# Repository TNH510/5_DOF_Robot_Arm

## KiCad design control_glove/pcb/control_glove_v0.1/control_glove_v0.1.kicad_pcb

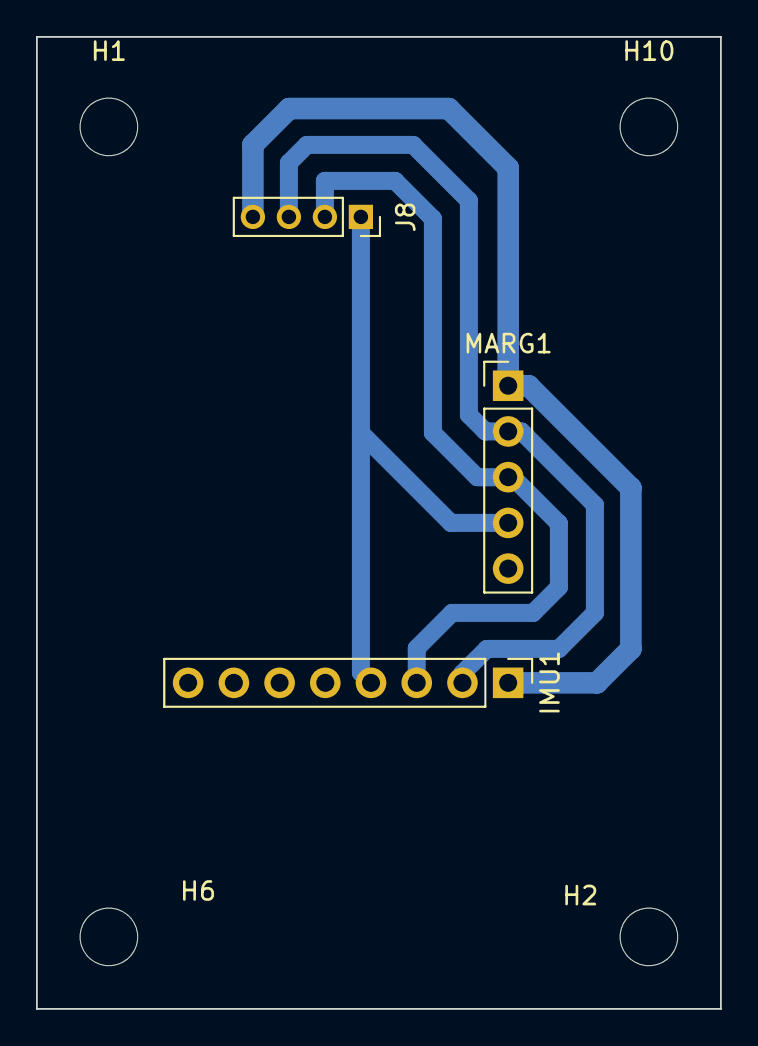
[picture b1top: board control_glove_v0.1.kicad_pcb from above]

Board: 2 copper layers, 38.0 x 54.0 mm, 7 parts (0 on the bottom side), 4 nets.

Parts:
H1, H2, H6, H10: MountingHole; MountingHole_3.2mm_M3
IMU1: GY-521; PinHeader_1x08_P2.54mm_Vertical
J8: Conn_01x04_Female; PinSocket_1x04_P2.00mm_Vertical
MARG1: HMC5883L; PinHeader_1x05_P2.54mm_Vertical

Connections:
unnamed: IMU1.1 (VCC), J8.4, MARG1.1 (VCC)
unnamed: IMU1.2 (GND), J8.3, MARG1.2 (GND)
unnamed: IMU1.3 (SCL), J8.2, MARG1.3 (SCL)
unnamed: IMU1.4 (SDA), J8.1, MARG1.4 (SDA)

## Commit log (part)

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2024-03-16 update: Design angle control schematic
2024-03-16 update: Angle follow set point success
2024-03-16 update: Add SFC program 6
2024-03-16 update: Test image processing on Matlab
2024-03-16 update: Add adapt 5 axis
2024-03-16 update: Control robot using apdative control through uart
2024-03-16 update: Test z_pos control adapt success
2024-03-17 update: Apply madgwickAHRS for IMU and MARG success
2024-03-17 update: finish detect edge image
2024-03-17 update: Optimize uart receive
2024-03-17 update: Optimize code for GUI
2024-03-17 update: Remove start frame
2024-03-23 update: Meeting 23/03
2024-03-23 update: Components list and caculate prices
2024-03-23 update: Complete schematic design
2024-03-23 fix: Merge conflict
2024-03-24 update: Test marg sensor calib
2024-03-24 Update: Done detect egde by canny method
2024-03-24 Update: change name function
2024-03-29 update: Calib IMU success
2024-03-30 update: Add QMC5883L datasheet
2024-03-30 update: Add QMC5883L sensor files
2024-03-30 update: Get MARG data success
2024-03-31 update: Read ADC very success
2024-03-31 update: setting.json
2024-03-31 Delete
2024-04-03 update: Change clock from 64 Mhz to 80 Mhz
2024-04-05 Update: complete Hough Transform
2024-04-05 update: Test quaternion
2024-04-06 update: Success caculate forward kinematic for glove
2024-04-06 Update: Success drawing edges
2024-04-06 update: Success caculate and display x, y, z pos from glove (need improve)
2024-04-07 update: Add MPU9250 files to reference
2024-04-07 update: Delete uneccessary files
2024-04-07 update: add comment code
2024-04-07 update: Complete list and connect all components
2024-04-07 update: Pins for PCB
2024-04-12 update: PCB setup and arange component positions
2024-04-13 update: Complete merging image processing
2024-04-14 update: Complete fix pcb
2024-04-15 update: Excel file
2024-04-15 refactor: Clean all
2024-04-18 update: Success calib for shoulder IMU
2024-04-18 update: Success calib for shoulder MARG
2024-04-18 update: Add low pass filter average for RV1
2024-04-18 fix: Wireless UART module do not respone
    Set Pin need to HIGH
2024-04-18 update: Add Wireless UART module note
2024-04-19 update: Success encrypt and decrypt data between device and MATLAB
2024-04-19 update: Test with python
2024-04-19 update: Complete test kinematic with shoulder and elbow
2024-04-20 update: Control glove space (not correct l1, l2)
2024-04-20 update: Test robot pos convert
2024-04-21 update: Add invert kinematic function
2024-04-21 update: Complete basic glove hardware v0.1 (need fixed size)
2024-05-02 ADD: file Testing Otsu's Method
2024-05-04 update: Update position and show on robot in GUI
2024-05-04 update: Optimize data transmission speed for UART
2024-05-04 Update: Apply Otsu method success.
2024-05-05 update: Vo pin
2024-05-05 update: Modify the limitation for angle of robot
2024-05-05 fix: Limitation for Z axis
2024-05-05 update: Try to use glove to control real Robot
2024-05-05 update: Test control robot over glove successfully
2024-05-05 Update: Success Auto Thresholding
2024-05-05 update: Create function for MoveL
2024-05-07 update: clear Hough Threshold.text
2024-05-07 Update: Copy file WindowApp to Image_processing
2024-05-07 update: Create trajectory for real Robot control
2024-05-07 fix: Change the TCP/IP port
2024-05-09 Update: convert from winform app to console app
2024-05-10 update: Design the transmission system at the wrist join
2024-05-10 update: Add basic content to control glove documents
2024-05-11 update: Create function to write angle data to plc
2024-05-11 update: Finish creating function to move 3 points for robot
2024-05-11 update: Add function in timer in order to test
2024-05-11 fix: Delete 1 line due to duplication
2024-05-11 update: Add glove_v0.1_part_1
2024-05-12 update: Change plc program
2024-05-12 update: Add 2 gear for control glove
2024-05-15 update: Add hole for imu module wires
2024-05-17 update: Change pcb size to 38 x 100
2024-05-18 update: Complete connect thanh_cang_tay and thanh_khuy_tay
2024-05-18 update: nothing
2024-05-18 update: Upload which need to be done for protect capstone project
2024-05-19 update: Add autocad file for mica cutting
2024-05-19 update: Connect all component completely
2024-05-19 update: Delete over defined error
2024-05-23 Update:Display the corner on Image
2024-05-24 update: Prepare files for mica cutting and 3d printing
2024-05-24 Update: complete calculate Mid Point object and angle object
2024-05-25 update: Finish testing move mutliple points with MoveJ
2024-05-25 update: Add element to control theta 5
2024-05-25 update: Re-cut mica
2024-05-26 update: Create robot_data for trajectory planning
2024-05-26 update: Transfer program from winform to console
2024-05-26 update: Export Japcobian Plus result
2024-05-26 update: Create function to move every 10 points
2024-05-31 update: Add SW1 and SW2 success
2024-05-31 update: Change UART module settings to reduce power consumption and I2C issues cause by lack of power
2024-06-01 update: Create workitem to do
2024-06-01 Update: Detect shape
2024-06-01 Nothing
2024-06-01 update: I'm try my best to filter noise in image, ye?
2024-06-02 fix: UART position data always zero
2024-06-02 update: Add crc-8-atm
2024-06-06 update: Bills for all
2024-06-06 update: Optimize uart module send 19 bytes at one time and use 210 ms
2024-06-07 update: Complete update nap pin
2024-06-07 update: Export .stl files
2024-06-07 update: Add 2D drawing for thanh cang tay, thanh khuyy tay and thanh noi
2024-06-08 update: Create python file to show raw data on graph
2024-06-08 update: Demonstrate the method of linear regression and circular regression
2024-06-09 docs: Update to design control robot arm algorithm
2024-06-09 update: Add K7 program to control velocity
2024-06-09 update: Add K7 program to control velocity Add adaptive velocity control
2024-06-09 update: Check jacobi
2024-06-09 update: Create function to using adaptive control with controlling velocity
2024-06-09 update: Test receive UART success
2024-06-09 update: Rename robot tool gui folder
2024-06-10 update: Fix conflict for gui c#
2024-06-10 update: Test linear regression function sucessfully
2024-06-10 fix: UART break when move control glove
2024-06-11 update: Add function to save polynomial_regression.csv
2024-06-14 update: Add custom gear 6 mm
2024-06-14 update: Add bearing 6 mm
2024-06-15 update: Save velocity and position to .csv file success
2024-06-15 update: omega 1, omega 2, omega look like stable
2024-06-15 update: Discovery new feature -- TabControl
2024-06-15 update: Create polynomial regression completely
2024-06-16 update: Create the final ver for image processing
2024-06-16 update: Enable velocity control
2024-06-16 fix: Velocity do not transmit to plc
2024-06-16 update: Not send stream command when hold left button
2024-06-16 update: Enable write to csv
2024-06-16 update: Reset raw data for test.csv
2024-06-16 update: Add hieu_packet to test uart
2024-06-17 update: Optimize GUI
2024-06-17 update: polynomial_regression on matlab
2024-06-17 update: test polyomial regression on matlab
2024-06-17 update: Test UART failed, need to optimize C#
2024-06-17 fix: UART error fixed
2024-06-17 update: Optimize low vel control
2024-06-18 docs: Add 6mm bearing datasheet
2024-06-19 update: Done the polynomial regression
2024-06-19 update: Complete basic concept design of v0.3
2024-06-19 update: Still facing polynomial regression algorthim
2024-06-20 update: Add red and green button
2024-06-20 update: detect point in hough matrix
2024-06-21 update: Optimize min angle to 60 degrees
2024-06-21 update: Fix all bug
2024-06-21 update: Clean code
2024-06-21 update: Add driver to control LED
2024-06-22 update: Test change system mode success
2024-06-22 update: Test send encode data success
2024-06-22 fix: Bug in low pass filter
2024-06-22 update: Add STL for 2 part of control glove
2024-06-22 update: Create low pass filter for stable the input data
2024-06-22 update: Success import glove.stl to view
2024-06-22 update: upload Doc proccessing image
2024-06-22 ADD: file .dll
2024-06-22 update: Complete take file dll from Loc
2024-06-23 update: Delete unused files
2024-06-23 update: Finish testing take data from csv to control robot trajectory Remember everytime to run -> Set speed for robot
2024-06-23 update: Add led indicator to check status of device
2024-06-23 update: - Finally create 100 points to load to PLC - Successfully load data to PLC with lower than 100 and greater than 100 points
2024-06-23 update: Draw 2d for dem mat bich and add some docs
2024-06-23 update: Export schematic file to .dwg success
2024-06-24 update: Test init yaw success and need to improve elbow angle
2024-06-24 update: Create gui to know connect to glove success or not
2024-06-24 update: Improve elbow angle accurency success
2024-06-24 update: Complete state machine for trajectory control
2024-06-24 update: Complete testing ONLY CONTROL STATUS
2024-06-24 update: Prepare files to mica cutting and 3d printing
2024-06-24 update: Create update 100 points for velocity create velocity function
2024-06-24 update: Modify velocity funtion
2024-06-24 docs: Complete basic content of electric drawing
2024-06-24 update: Create velocity conversion
2024-06-25 update: Alway send start or stop record cmd
2024-06-25 update: Complete content of electric drawing, need optimize line width
2024-06-25 update: Show picture on Tool
2024-06-25 update: Create function to load image
2024-06-25 update: Create raw data for 8 points
2024-06-25 update: Successfully testing moving to the last point
2024-06-26 update: Finish testing converting image without losing data
2024-06-26 update: create home position for robot finish state machine for plc trajectory
2024-06-26 update: Finish testing robot control
2024-06-27 update: Complete conveyor plc code v15.0
2024-06-28 update: Unknow commit 27-6
2024-06-28 update: Complete basic 6 drawings
2024-06-28 update: Them phan phan tich kich thuoc co khi va chuan bi tinh luc tai truc
2024-06-28 update: doc
2024-06-29 update: Convert all part
2024-06-29 update: Firmware architector and frame
2024-06-29 update: Add content for WPF
2024-06-29 update: Change some direction in GUI
2024-06-29 update: ađ Circle detection
2024-06-29 update: Only use select button
2024-06-29 update: Create csv and update code
2024-06-29 update: Test buoi toi t7
2024-06-29 update: Add so do luc
2024-06-30 update: Complete sensor chart and
2024-06-30 update: Update current final report
2024-06-30 update: Finish seeding data and test system control
2024-06-30 update: Add moment data
2024-06-30 update: Add link video do an tot nghiep
2024-06-30 update: Create content for mai_bao_cao
2024-07-01 update: Xong phan calib va li thuyet
2024-07-01 update: Writing final report
2024-07-01 update: Writing final-report
2024-07-01 update: complete report băng tải và cảm biến.
2024-07-01 update: writing final doc
2024-07-03 update: Xong chuong 1
2024-07-03 update: Tinh xong phan banh rang va truc
2024-07-03 update: doc XLA
2024-07-03 update: Xong phan tinh ma tran xoay gang tay
2024-07-04 update: dócs
2024-07-04 update: docs
2024-07-04 update: tong hop ban ve dien
2024-07-05 update: Rename drawing prepare for final clear
2024-07-05 update: Hoan thanh 70% tat ca ban ve
2024-07-05 update: Add final test data
2024-07-05 update: Rename for clean meaning
2024-07-05 docs: Them bia va cac giay to
2024-07-05 update: List all content
2024-07-05 update: Hoan thanh format co ban cho do an tot nghiep
2024-07-05 update: Finish editing parameter for joints in Solidworks
2024-07-06 update: Create butotn for controlling data
2024-07-06 update: lựa chọn giác hút
2024-07-06 update: kết quả phần thực hiện hệ thống 5.1.1
2024-07-06 update: create csv
2024-07-07 docs: Sua hinh thuc
2024-07-07 update: new file
2024-07-07 update:file
2024-07-07 update: Xong noi dung cho toan bo ban ve
2024-07-07 update: Clean autocad files
2024-07-07 docs: Add ban ve A0 cho robot 5 bac
2024-07-08 update: Tong hop full ban ve va danh so bang, hinh anh
2024-07-08 update: Xong phan danh so hinh, bang, cong thuc
2024-07-08 update: Hoan thanh phan lien ket ca 3 lai voi nhau
2024-07-11 update: Them so hieu vao ban ve lap
